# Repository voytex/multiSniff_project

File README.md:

# multiSniff Masters Project

## General
Repository for my Master`s project called __[Multiprotocol Sniffer And Analyzer](https://www.vut.cz/studenti/zav-prace/detail/159103)__. 

The subject of this work is design of a device that captures Bluetooth Low Energy or IEEE 802.15.4 frames and sends them via Ethernet bus to a computer for subsequent analysis using Wireshark. The device is based on the CC2652RB microchip from Texas Instruments, which is accompanied by the WIZnet W5500 Ethernet interface. This repository includes MCU [software](./source), HTML code for web-based [control panel](./flashbins/index.html) and Wireshark [dissector](./wireshark/msniff.lua).

## Hardware Used
* TI CC2652RB LaunchPad for prototyping and SW development
* WIZnet W5500 with RJ-45 connector for Ethernet interface (SPI communication)
* SSD1306 OLED display (I2C communication)

## Results
### Prototype photo

### Dashboard screenshot

### Captured BLE traffic

<table>
  <tr>
    <td>
      black line
    </td>
    <td>
      sum of all BLE traffic (advertising channel)  
    </td>
  </tr>
  <tr>
    <td>
      blue line
    </td>  
    <td>
      advertising of BLE enabled coffee machine      
    </td>
  </tr>
  <tr>
    <td>
      red line    
    </td>
    <td>
    advertising of ESP32 turned on and off during test capture    
  </td>
  </tr>
</table>

## Other Links
* [Bachelor`s Project (MIDI over Ethernet)](https://github.com/voytex/MoE_firmware)

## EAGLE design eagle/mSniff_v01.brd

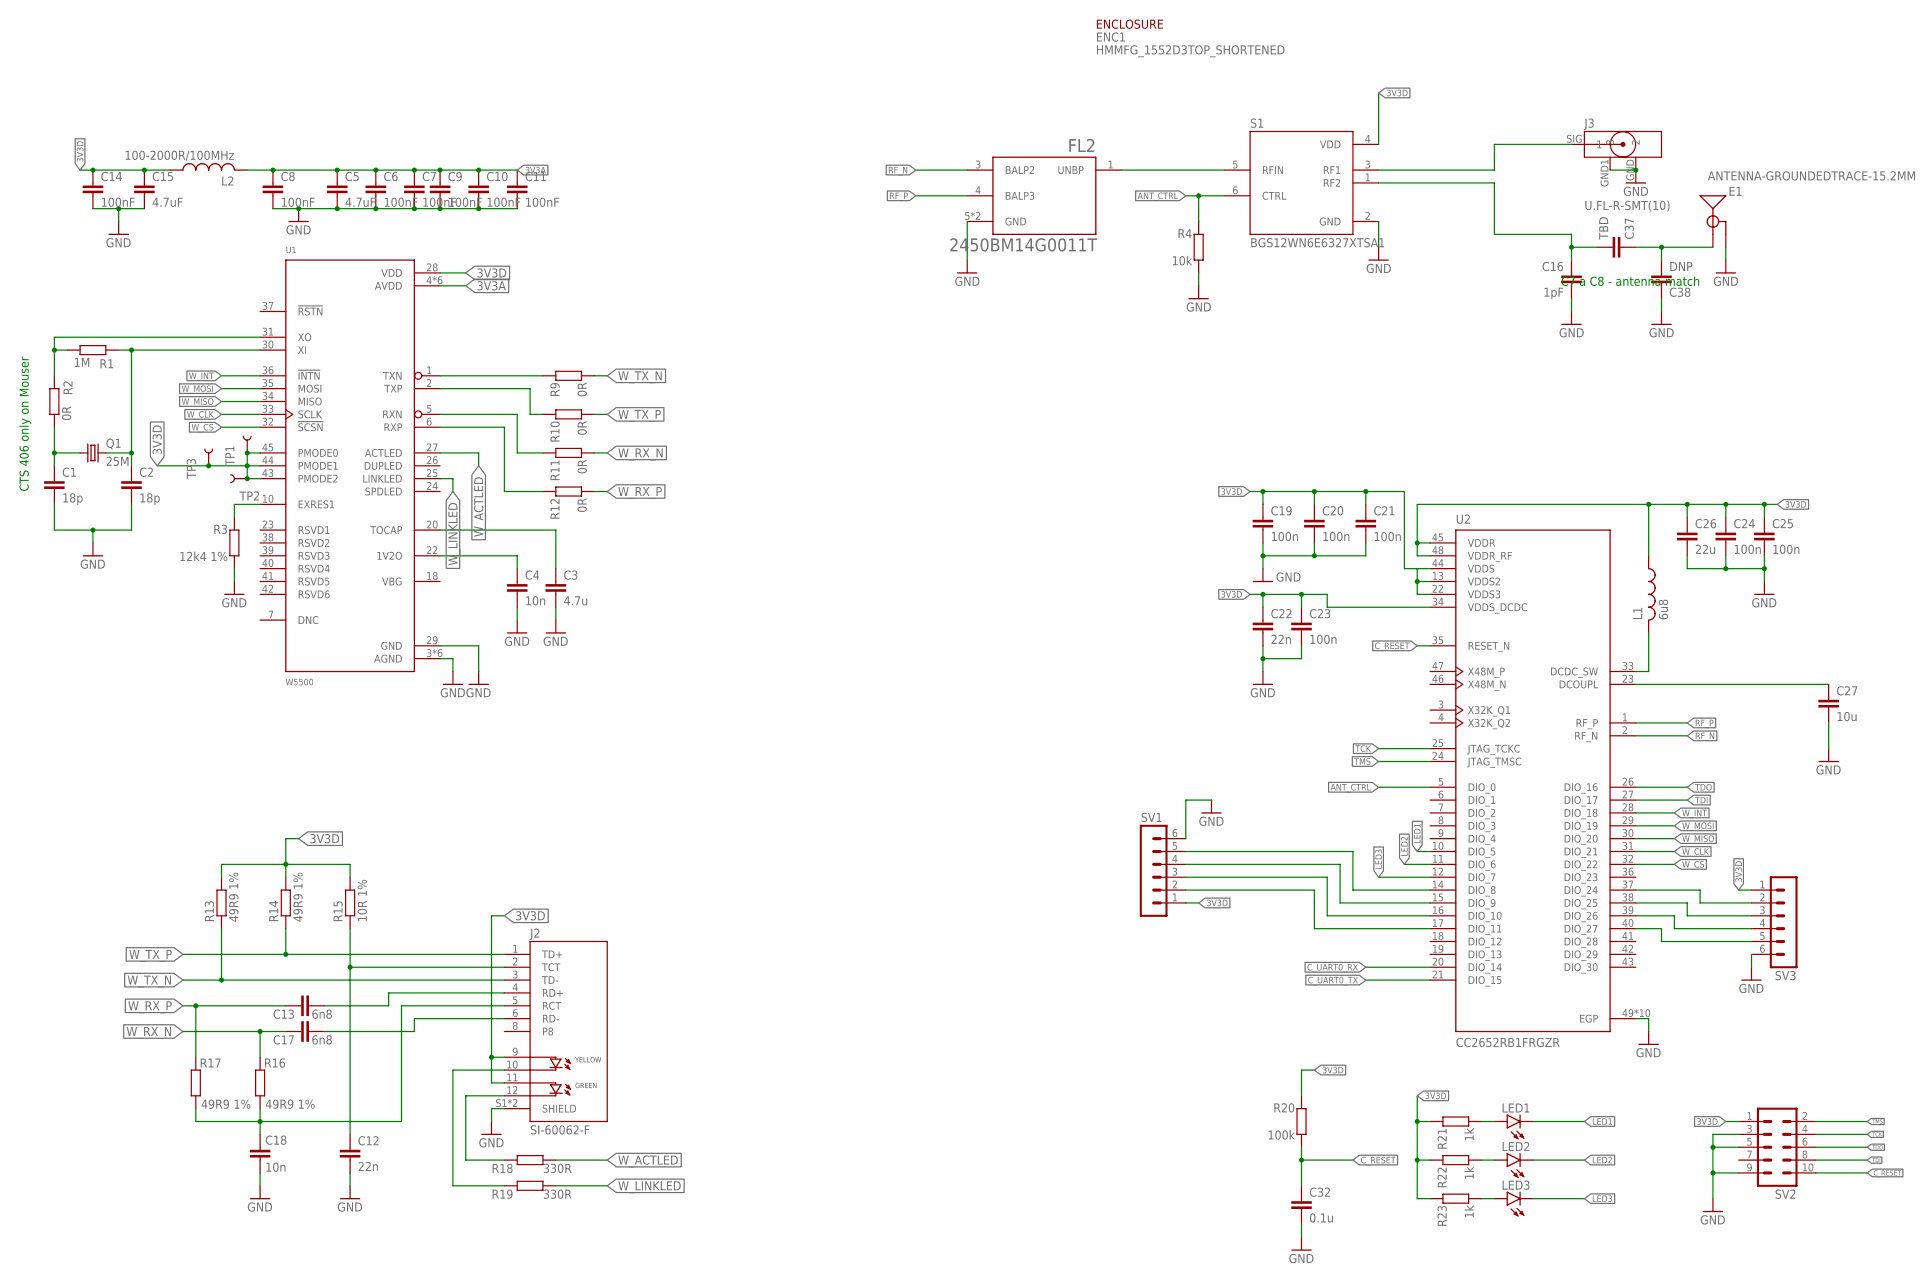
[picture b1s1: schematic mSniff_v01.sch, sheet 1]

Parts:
C1, C2: 18p; 0603REC_C
C3: 4.7u; 0603REC_C
C4, C18: 10n; 0603REC_C
C5, C15: 4.7uF; 0805REC_C
C6, C7, C8, C9, C10, C11, C14: 100nF; 0603REC_C
C12, C22: 22n; 0603REC_C
C13, C17: 6n8; 0603REC_C
C16: 1pF; 0402REC_C
C19, C20, C21, C23, C24, C25: 100n; 0603REC_C
C26: 22u; 0603REC_C
C27: 10u; 0603REC_C
C32: 0.1u; 0603REC_C
C37: TBD; 0402REC_C
C38: DNP; 0402REC_C
E1: ANTENNA-GROUNDEDTRACE-15.2MM; TRACE_ANTENNA_2.4GHZ_15.2MM
ENC1: HMMFG_1552D3TOP_SHORTENED; 1552D3_TOP_SHORT
FL2: 2450BM14G0011T; BALUN_2450BM14G0011T
J2: SI-60062-F; BEL_SI-60062-F
J3: U.FL-R-SMT(10)
L1: 6u8; 0805REC_L
L2: 100-2000R/100MHz; 0603REC_L
LED1, LED2, LED3: LEDCHIPLED_0603; CHIPLED_0603
Q1: 25M; CTS406
R1: 1M; 0603REC_R
R2, R9, R10, R11, R12: 0R; 0603REC_R
R3: 12k4 1%; 0603REC_R
R4: 10k; 0603REC_R
R13, R14, R16, R17: 49R9 1%; 0603REC_R
R15: 10R 1%; 0603REC_R
R18, R19: 330R; 0603REC_R
R20: 100k; 0603REC_R
R21, R22, R23: 1k; 0603REC_R
S1: BGS12WN6E6327XTSA1; SW_BGS12WN6E6327XTSA1
SV1, SV3: MA06-1
SV2: MA05-2SMD127; MA05-2-SMD127-GPEC214
TP1, TP2, TP3: TEST-POINT3; PAD.03X.03
U1: W5500; QFP50P900X900X160-48N
U2: CC2652RB1FRGZR; QFN50P700X700X100-49N

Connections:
3V3A: C5.1, C6.1, C7.1, C8.1, C9.1, C10.1, C11.1, L2.2, U1.4 (AVDD), U1.8 (AVDD), U1.11 (AVDD), U1.15 (AVDD), U1.17 (AVDD), U1.21 (AVDD)
3V3D: C14.1, C15.1, C19.1, C20.1, C21.1, C22.1, C23.1, C24.1, C25.1, C26.1, J2.9 (YA), J2.11 (GA), L1.1, L2.1, R13.2, R14.2, R15.2, R20.2, R21.2, R22.2, R23.2, S1.4 (VDD), SV1.1, SV2.1, SV3.1, TP1.P$1, TP2.P$1, TP3.P$1, U1.28 (VDD), U1.43 (PMODE2), U1.44 (PMODE1), U1.45 (PMODE0), U2.13 (VDDS2), U2.22 (VDDS3), U2.34 (VDDS_DCDC), U2.44 (VDDS), U2.45 (VDDR), U2.48 (VDDR_RF); also elsewhere on the board
ANT_CTRL: R4.2, S1.6 (CTRL), U2.5 (DIO_0)
C_RESET: C32.1, R20.1, SV2.10, U2.35 (RESET_N)
C_UART0_RX: U2.20 (DIO_14); also elsewhere on the board
C_UART0_TX: U2.21 (DIO_15); also elsewhere on the board
GND: C1.2, C2.2, C3.2, C4.2, C5.2, C6.2, C7.2, C8.2, C9.2, C10.2, C11.2, C12.2, C14.2, C15.2, C16.2, C18.1, C19.2, C20.2, C21.2, C22.2, C23.2, C24.2, C25.2, C26.2, C27.2, C32.2, C38.1, E1.GND, FL2.5 (GND), FL2.6 (GND), J2.S1 (SHIELD), J2.S2 (SHIELD), J3.GND (2), J3.GND1 (3), R3.1, R4.1, S1.2 (GND), SV1.6, SV2.3, SV2.5, SV2.9, SV3.6, U1.3 (AGND), U1.9 (AGND), U1.14 (AGND), U1.16 (AGND), U1.19 (AGND), U1.29 (GND), U1.48 (AGND), U2.49 (EGP), U2.50 (EGP), U2.51 (EGP), U2.52 (EGP), U2.53 (EGP), U2.54 (EGP), U2.55 (EGP), U2.56 (EGP), U2.57 (EGP), U2.58 (EGP); also elsewhere on the board
LED1: LED1.C, U2.10 (DIO_5)
LED2: LED2.C, U2.11 (DIO_6)
LED3: LED3.C, U2.12 (DIO_7)
unnamed: C2.1, Q1.3 (2), R1.2, U1.30 (XI)
unnamed: R1.1, R2.2, U1.31 (XO)
unnamed: C1.1, Q1.1, R2.1
unnamed: C4.1, U1.22 (1V2O)
unnamed: R3.2, U1.10 (EXRES1)
unnamed: C16.1, C37.2, S1.1 (RF2)
unnamed: C3.1, U1.20 (TOCAP)
unnamed: SV1.5, U2.14 (DIO_8)
unnamed: FL2.1 (UNBP), S1.5 (RFIN)
unnamed: SV1.4, U2.15 (DIO_9)
unnamed: SV1.3, U2.16 (DIO_10)
unnamed: SV1.2, U2.17 (DIO_11)
unnamed: J3.SIG (1), S1.3 (RF1)
unnamed: SV3.2, U2.37 (DIO_24)
unnamed: C37.1, C38.2, E1.ANT (SIGNAL)
unnamed: SV3.3, U2.38 (DIO_25)
unnamed: SV3.4, U2.39 (DIO_26)
unnamed: C12.1, J2.2 (TCT), R15.1
unnamed: SV3.5, U2.40 (DIO_27)
unnamed: C27.1, U2.23 (DCOUPL)
unnamed: J2.12 (GK), R18.2
unnamed: C18.2, J2.5 (RCT), R16.1, R17.1
unnamed: J2.10 (YK), R19.2
unnamed: L1.2, U2.33 (DCDC_SW)
unnamed: LED1.A, R21.1
unnamed: LED2.A, R22.1
unnamed: LED3.A, R23.1
RD_N: C17.2, J2.6 (RD-)
RD_P: C13.2, J2.4 (RD+)
RF_N: FL2.3 (BALP2), U2.2 (RF_N)
RF_P: FL2.4 (BALP3), U2.1 (RF_P)
RX_N: R11.2, U1.5 (RXN)
RX_P: R12.2, U1.6 (RXP)
TCK: SV2.4, U2.25 (JTAG_TCKC)
TDI: SV2.8, U2.27 (DIO_17)
TDO: SV2.6, U2.26 (DIO_16)
TMS: SV2.2, U2.24 (JTAG_TMSC)
TX_N: R9.2, U1.1 (TXN)
TX_P: R10.2, U1.2 (TXP)
W_ACTLED: R18.1, U1.27 (ACTLED)
W_CLK: U1.33 (SCLK), U2.31 (DIO_21)
W_CS: U1.32 (!SCSN), U2.32 (DIO_22)
W_INT: U1.36 (!INTN), U2.28 (DIO_18)
W_LINKLED: R19.1, U1.25 (LINKLED)
W_MISO: U1.34 (MISO), U2.30 (DIO_20)
W_MOSI: U1.35 (MOSI), U2.29 (DIO_19)
W_RX_N: C17.1, R11.1, R16.2
W_RX_P: C13.1, R12.1, R17.2
W_TX_N: J2.3 (TD-), R9.1, R13.1
W_TX_P: J2.1 (TD+), R10.1, R14.1

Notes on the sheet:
CTS 406 only on Mouser
C7 a C8 - antenna match

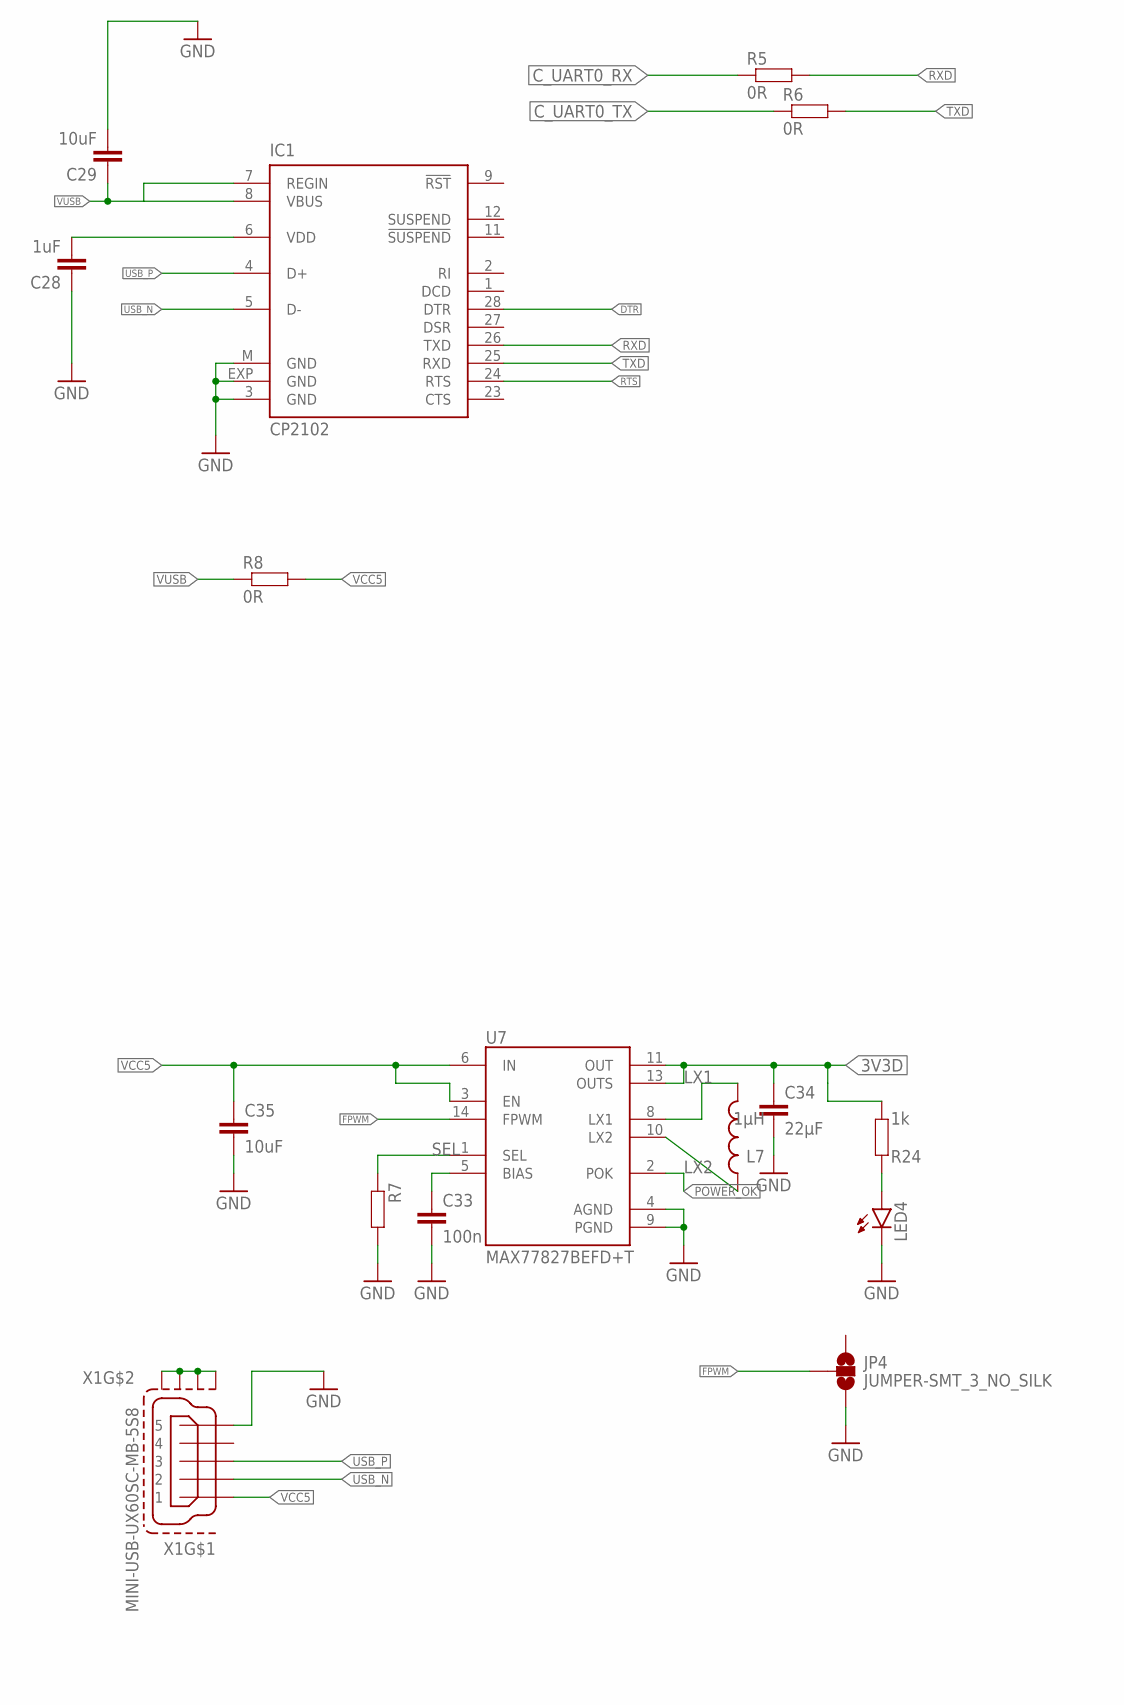
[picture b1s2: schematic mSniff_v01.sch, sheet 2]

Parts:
C28: 1uF; 0603REC_C
C29, C35: 10uF; 0603REC_C
C33: 100n; 0603REC_C
C34: 22μF; 0603REC_C
IC1: CP2102; MLP28
JP4: JUMPER-SMT_3_NO_SILK; SMT-JUMPER_3_NO_SILK
L7: 1μH; 1008REC_L
LED4: LEDCHIPLED_0603; CHIPLED_0603
R5, R6, R8: 0R; 0603REC_R
R7: R_0603REC; 0603REC_R
R24: 1k; 0603REC_R
U7: MAX77827BEFD+T; CONV_MAX77827BEFD+T
X1: MINI-USB-UX60SC-MB-5S8; HIROSE_UX60SC-MB-5S8

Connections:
3V3D: C34.1, R24.1, U7.11 (OUT), U7.13 (OUTS); also elsewhere on the board
BIAS: C33.1, U7.5 (BIAS)
C_UART0_RX: R5.1; also elsewhere on the board
C_UART0_TX: R6.1; also elsewhere on the board
DTR: IC1.28 (DTR)
FPWM: JP4.2, U7.14 (FPWM)
GND: C28.1, C29.2, C33.2, C34.2, C35.2, IC1.3 (GND), IC1.EXP (GND), IC1.M (GND), JP4.3, LED4.C, R7.2, U7.4 (AGND), U7.9 (PGND), X1.5; also elsewhere on the board
LX1: L7.2, U7.8 (LX1)
LX2: L7.1, U7.10 (LX2)
unnamed: LED4.A, R24.2
unnamed: X1.S1, X1.S2, X1.S3, X1.S4
unnamed: C28.2, IC1.6 (VDD)
POWER_OK: U7.2 (POK)
RTS: IC1.24 (RTS)
RXD: IC1.26 (TXD), R5.2
SEL: R7.1, U7.1 (SEL)
TXD: IC1.25 (RXD), R6.2
USB_N: IC1.5 (D-), X1.2
USB_P: IC1.4 (D+), X1.3
VCC5: C35.1, R8.2, U7.3 (EN), U7.6 (IN), X1.1
VUSB: C29.1, IC1.7 (REGIN), IC1.8 (VBUS), R8.1

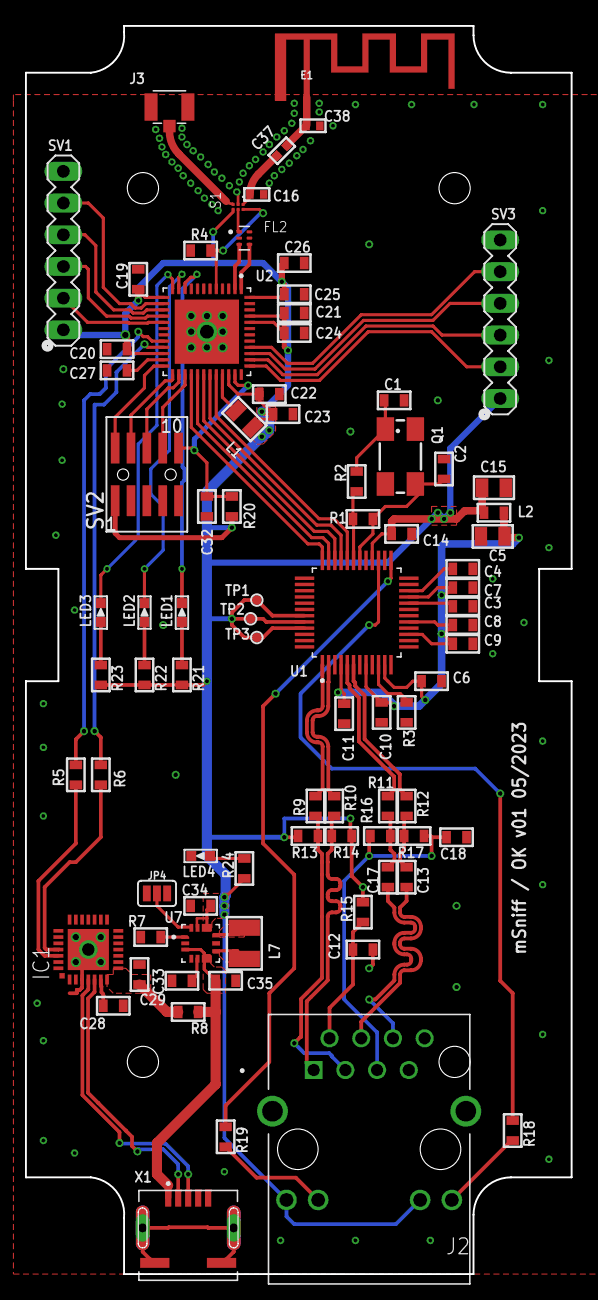
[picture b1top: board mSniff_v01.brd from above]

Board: 2 copper layers, 43.7 x 100.0 mm, 85 parts (1 on the bottom side), 74 nets.

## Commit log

2023-09-11 initial commit
    adding design and bit of radio API
2023-09-11 initRXcmd
2023-09-11 beginRX
2023-09-17 openradiocore
2023-09-17 more functions
2023-09-17 adding bits and pieces
2023-09-17 Dashboard
2023-09-17 html to bin
2023-09-25 Design edit, beginRX, stopRX
2023-09-25 bugfixes
2023-10-02 Log module started
2023-10-03 Log function dev
2023-10-03 changed project structure
2023-10-03 structural refinments
2023-10-03 added radio queue by TI
2023-10-03 getting to function, bits and pieces to log
2023-11-17 SSD1306 driver development 1
2023-11-17 SSD1306 driver dev part 2
    Not sure about the LcdBufferInclStreamByte is set and manioulated properly
2023-11-17 Docs for SSD1306
2023-11-23 SSD1306 somewhat working
    DrawLine zlobí a InvertString není moc pěkné
2023-11-23 Fixed DrawLine
2023-11-23 Fixed InvertedDraw
2023-11-25 GUI
    GUI driver encapsulating SSD1306 LL driver
2023-11-25 minor restructuralization
    oled_guit moved to source/.
2023-11-26 Docs for GUI
2023-11-26 minor fixes
2023-11-27 Fixed GUI_ChangeChannel
    not absolutely elegant, but working without any external library.
2023-11-27 ethernet driver added
2023-12-07 fixed spi and i2c coexistence
    When adding SPI driver in SysConfig, I2C pins get shifted without any warning whatsoever. Thank You Texas Instruments.
2023-12-07 fixed hw to reflect changes intriduced by adding SPI driver
2023-12-12 Startup vectors bin file creation
2023-12-12 init task probably done and proablier working
2024-01-04 IPAddress_to_string edited
2024-01-05 Minor fix for GUI
2024-01-05 Html filler
    Už teď vím že to nebude fungovat ale co už
2024-01-05 html progress
    no furt nějako nevím
2024-01-06 html copier and parser done
    ?
2024-01-06 bit of docs
2024-01-06 docs and cosmetics
2024-01-06 html ressurection and fix according to new system
2024-01-06 web dashboard edit
2024-01-06 polish
    kto polak?
2024-01-06 moved html code to flash memory
2024-01-06 added http preamble
2024-01-13 working again
    Finally! After days of not working, it began... working...
2024-01-20 Reset procedure and STV clarification
2024-01-21 Init task nearly done
2024-01-21 bits and pieces
2024-01-30 finished html engine and edited index.htmlo
2024-02-04 edited STV map (order and number of entries)
2024-02-05 improved HTTP server (changing properties)
2024-02-17 lets talk
    okay, now... I have been struggling all day to make it work. Debugging and stepping in and out of functions. Absolutely honestly - I have no idead why that works now and was not working earlier, I ha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
2024-02-17 implemented DHCP status visible in dashboard
2024-02-18 implemented statistics
    sprintf uses sooooo many resources! consider rewriting (at the end, i just need uint16_t -> string a int8_t -> string... how hard could it be?!)
2024-02-19 added functionality to start and stop via web dashboard
2024-03-11 Interrupt server now partialy working
    cannot reset SIR and SnIR - no idea why, it worked, I changed nothing, then it sstopped working. This is stresful...
2024-04-03 somehow working
2024-04-03 minor html fixes, STV add channel
2024-04-04 omgicannotbelieveitiskindaworking
2024-04-04 well actually - turning RF CMDs off and on is working. Withou MCU restart
2024-04-04 BLE channel switching working
2024-04-04 IEEE802.15.4 channel switching
2024-04-05 Bits and pieces, close to baseline
2024-04-07 docs
2024-04-09 nearly baseline
2024-04-13 Formatting and bit of documentation
2024-04-13 formatting
2024-04-27 html minor edit
2024-04-27 html minor improvements
2024-04-28 baseline version
2024-04-28 dissector upload
2024-05-06 test capture graphed
2024-05-06 flow_graph
2024-05-11 eagle exports
2024-05-11 better eagle export
2024-05-19 eagle

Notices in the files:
parts and their libraries:
SparkFun-RF: Licensing: Creative Commons ShareAlike 4.0 International - https://creativecommons.org/licenses/by-sa/4.0
